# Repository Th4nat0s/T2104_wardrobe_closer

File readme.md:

WardRobe CLOSER
===============

Detect open doors and Bip
--------------------------

### Arduino
Usb connection 
arduino framework 

### Attiny84
SPI Through BusPirate 
arduino framework 

Consumption
-----------
On Attiny25 @ 1Mhz  
Sleeping: 6,6µA  
Beeping : 1.2mA  

Expectation on Sony CR-2032 - Batterie CR2032 - Li - 220 mAh  
10 Mn Beeping daily  

Tips
----
`./serial` launch serial console through buspirate  
`pio run -t fuses` set the fuses  
`pio run -t upload -e atiny25` upload  a specific release version without serial debug  
`pio platform update --dry-run` check for updates

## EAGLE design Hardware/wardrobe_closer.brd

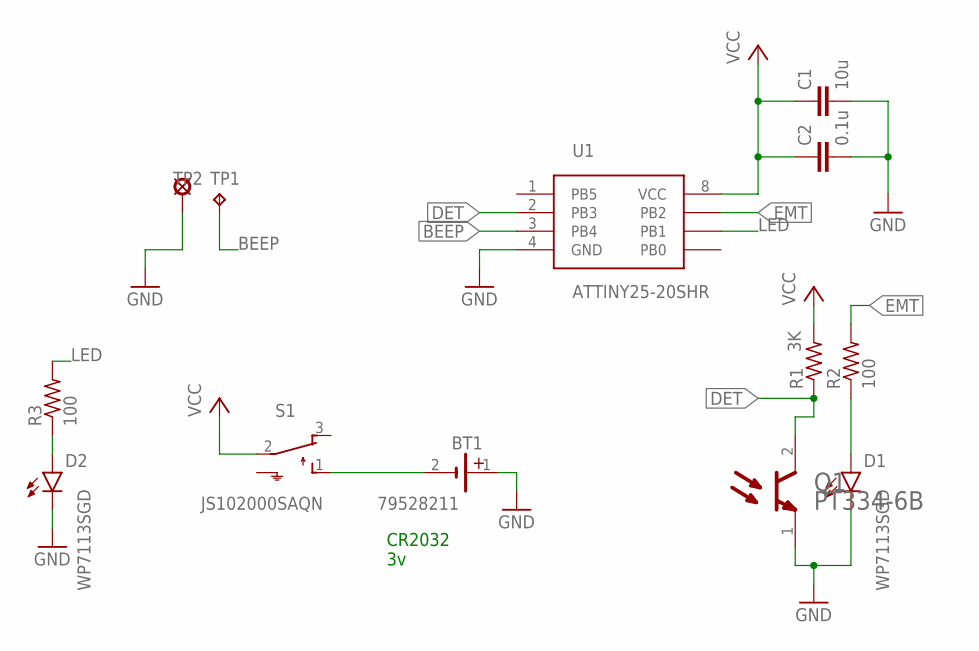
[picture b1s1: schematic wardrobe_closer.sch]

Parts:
BT1: 79528211
C1: 10u; C0603K
C2: 0.1u; C0603K
D1, D2: WP7113SGD; RADIAL_5MM
Q1: EVERLIGHT_PT334-6BEVERLIGHT_PT334-6B_0_0; EVERLIGHT_PT334-6B_0
R1: 3K; R0603
R2, R3: 100; R0603
S1: JS102000SAQN
TP1: TPB1,27; B1,27
TP2: LSP10
U1: ATTINY25-20SHR; SOIC-8

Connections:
BEEP: TP1.TP, U1.3 (PB4)
DET: Q1.2 (COLLECTOR), R1.1, U1.2 (PB3)
EMT: R2.2, U1.7 (PB2)
GND: BT1.1 (+), C1.2, C2.2, D1.C, D2.C, Q1.1 (EMITTER), TP2.MP, U1.4 (GND)
LED: R3.2, U1.6 (PB1)
unnamed: D1.A, R2.1
unnamed: BT1.2 (-), S1.1
unnamed: D2.A, R3.1
VCC: C1.1, C2.1, R1.2, S1.2, U1.8 (VCC)

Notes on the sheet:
CR2032 3v

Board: 2 copper layers, 13 parts (1 on the bottom side), 9 nets, no tracks yet.

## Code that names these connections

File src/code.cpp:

/*
  __      __                  ._____________      ___.
 /  \    /  \_____ _______  __| _/\______   \ ____\_ |__   ____
 \   \/\/   /\__  \\_  __ \/ __ |  |       _//  _ \| __ \_/ __ \
  \        /  / __ \|  | \/ /_/ |  |    |   (  <_> ) \_\ \  ___/
   \__/\  /  (____  /__|  \____ |  |____|_  /\____/|___  /\___  >
        \/  ______\/.  __      \/         \/           \/     \/
            \_   ___ \|  |   ____  ______ ___________
            /    \  \/|  |  /  _ \/  ___// __ \_  __ \
            \     \___|  |_(  <_> )___ \\  ___/|  | \/
             \______  /____/\____/____  >\___  >__|
                    \/                \/     \/
                          Copyleft Thanat0s Since april 2021

  For all the kids who did not close their fuck**g WardRobes !!


  Code for Attiny25 microcontroller
  https://github.com/Th4nat0s/T2104_wardrobe_closer.

                               ATMEL Attiny25 / (ARDUINO)

                                         +-\/-+
        PCINT5/RESET/ADC0/dW        PB5 1|*   |8 VCC
 PCINT3/XTAL1/CLKI/OC1B/ADC3 (A3/3) PB3 2|    |7 PB2 (A1/2) SCK/SCL/USKC/TO/PCINT2
 PCINT4/XTAL2/CLKO/OC1B/ADC2 (A2/4) PB4 3|    |6 PB1 (1)    MISO/DO/AIN1/OC0B/OC1A/PCINT1
                                    GND 4|    |5 PB0 (0)    MOSI/DI/SDA/AIN0/OC0A/OC1A/AREF/PCINT0
                                         +----+
What does it do...
 Read door status of Wardrobe every minutes
 If open more than 5min
 Beep Until a kid close the Wardrobe !

https://enavarro.eu/exploration-des-sleep-mode-du-attiny85.html

*/

#include <Arduino.h>
#include <avr/sleep.h>

// Connectique
// Connect to input of TRCS5000
#define DET A3

// Connect to LED of TRCS5000
// In Attiny25 #define EMT 1
#define EMT 2

// To Buzzer
#define BEEP 4

// To Battery Led
#define LED 1

// Variables
int view;  // DAC read for sensor
int warning;
bool door = false;  // Door status, True is open
bool alert = false;
#define maxcount 5 // number of try before buzzing
int f_wdt = 0;  // out of sleep

// Define
#define TH_OPEN 210


// time base is 6=1 sec,7=2 sec, 8=4 sec, 9= 8sec
// time_base x time_mult = work loop delay
#define time_mult 8
#define time_base 9


// Routines to set and clear bits (used in the sleep code)
#ifndef cbi
#define cbi(sfr, bit) (_SFR_BYTE(sfr) &= ~_BV(bit))
#endif
#ifndef sbi
#define sbi(sfr, bit) (_SFR_BYTE(sfr) |= _BV(bit))
#endif

// WDTCR in atmega is named WDTCSR
#ifndef WDTCR
#define WDTCR WDTCSR
#endif

// 6=1 sec,7=2 sec, 8=4 sec, 9= 8sec
void setup_watchdog(int ii) {
  byte bb;
  if (ii > 9 ) ii=9;
  bb=ii & 7;
  if (ii > 7) bb|= (1<<5);
  bb|= (1<<WDCE);

  MCUSR &= ~(1<<WDRF);
  // start timed sequence
  WDTCR |= (1<<WDCE) | (1<<WDE);
  // set new watchdog timeout value
  WDTCR = bb;
  WDTCR |= _BV(WDIE);
}

// Watchdog Interrupt Service / is executed when watchdog timed out
ISR(WDT_vect) {
  f_wdt++;  // Increment timer
}

void setup()
{
  // initialize LED digital pin as an output.
  #ifdef __PLATFORMIO_BUILD_DEBUG__
  Serial.begin(9600);
  Serial.println("System Start");
  Serial.flush();
  #endif
  pinMode(LED,OUTPUT);
  setup_watchdog(time_base); // how many ~ Sec for 1 sleep loop.
  for (int i = 1; i <= 15; i++) {
    digitalWrite(LED,HIGH);
    delay(500);
    digitalWrite(LED,LOW);
    delay(500);
    }
}

void read_sensor()
// Read the sensor twice with or 
// Without led on to remove noise
{
  digitalWrite(EMT,HIGH);
  delayMicroseconds(500);
  view=analogRead(DET);  // 1ere lecture avec Led ir on
  digitalWrite(EMT,LOW);
  delayMicroseconds(500);
  view=analogRead(DET) - view;  // 2eme lecture avec Led ir off
  #ifdef __PLATFORMIO_BUILD_DEBUG__
  Serial.print("Score Read:");
  Serial.println(view);
  Serial.flush();
  #endif
  if (view > TH_OPEN){
    door = false;
    alert = false;
    warning = 0;
  } else {
    door = true;
  }
}

void main_loop()
{
  pinMode(EMT,OUTPUT);  // Reactivate out port
  pinMode(LED,OUTPUT);  // Reactivate out port
  delayMicroseconds(500);
  read_sensor();
  #ifdef __PLATFORMIO_BUILD_DEBUG__
  Serial.print("Main Loop, Door Status:");
  Serial.println(door);
  Serial.print("Main Loop, Warning Status:");
  Serial.println(warning);
  Serial.flush();
  #endif
  if (door == true){
    warning++;
    if (warning >= maxcount) {
      alert = true;
    }
  }
  while (alert == true) {
     // If more than N minutes
     #ifdef __PLATFORMIO_BUILD_DEBUG__
     Serial.println("Alert Door Open");
     Serial.flush();
     #endif
     tone(BEEP, 2600, 500);  // Tone 1, 0,5 Sec.
     delay(500);
     tone(BEEP, 1500, 500); // Tone 2, 0,5 Sec
     delay(1500);          // Silence 1 Sec.
     read_sensor();
    }
  pinMode(EMT,INPUT);  // Activate port In to lower consumpion
  pinMode(LED,INPUT);  // Activate port In to lower consumpion
}

// set system into the sleep state
// system wakes up when wtchdog is timed out
void system_sleep() {
  cbi(ADCSRA,ADEN);                    // switch Analog to Digitalconverter OFF
  set_sleep_mode(SLEEP_MODE_PWR_DOWN); // sleep mode is set here
  sleep_enable();                      // activate sleep
  sleep_mode();                        // System actually sleeps here
  sleep_disable();                     // System continues execution here when watchdog timed out
  sbi(ADCSRA,ADEN);                    // switch Analog to Digitalconverter ON
}

void fake_sleep()
{
  delay(1000);
  f_wdt++;
  #ifdef __PLATFORMIO_BUILD_DEBUG__
  Serial.print("Wdt timer");
  Serial.println(f_wdt);
  Serial.flush();
  #endif
}


void loop()
{
  // 8 Sec x 8 = around 64 seconds
  if (f_wdt>=time_mult) {  // wait for timed out watchdog / flag is set when a watchdog timeout occurs
    #ifdef __PLATFORMIO_BUILD_DEBUG__
    Serial.println("Wdt timer Match count");
    Serial.flush();
    #endif
    main_loop();  // call real loop
    f_wdt=0;      // reset timing loop flag
  }
  //fake_sleep();
  #ifdef __PLATFORMIO_BUILD_DEBUG__
  Serial.println("Sleeping Loop");
  Serial.flush();
  #endif
  system_sleep();  // Send the unit to sleep
}

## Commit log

2021-04-22 hardware push
2021-04-22 upd gitignore
2021-04-22 First Code
2021-04-26 code ready
2021-05-04 working code
2021-05-05 Update design
2021-05-06 add led
